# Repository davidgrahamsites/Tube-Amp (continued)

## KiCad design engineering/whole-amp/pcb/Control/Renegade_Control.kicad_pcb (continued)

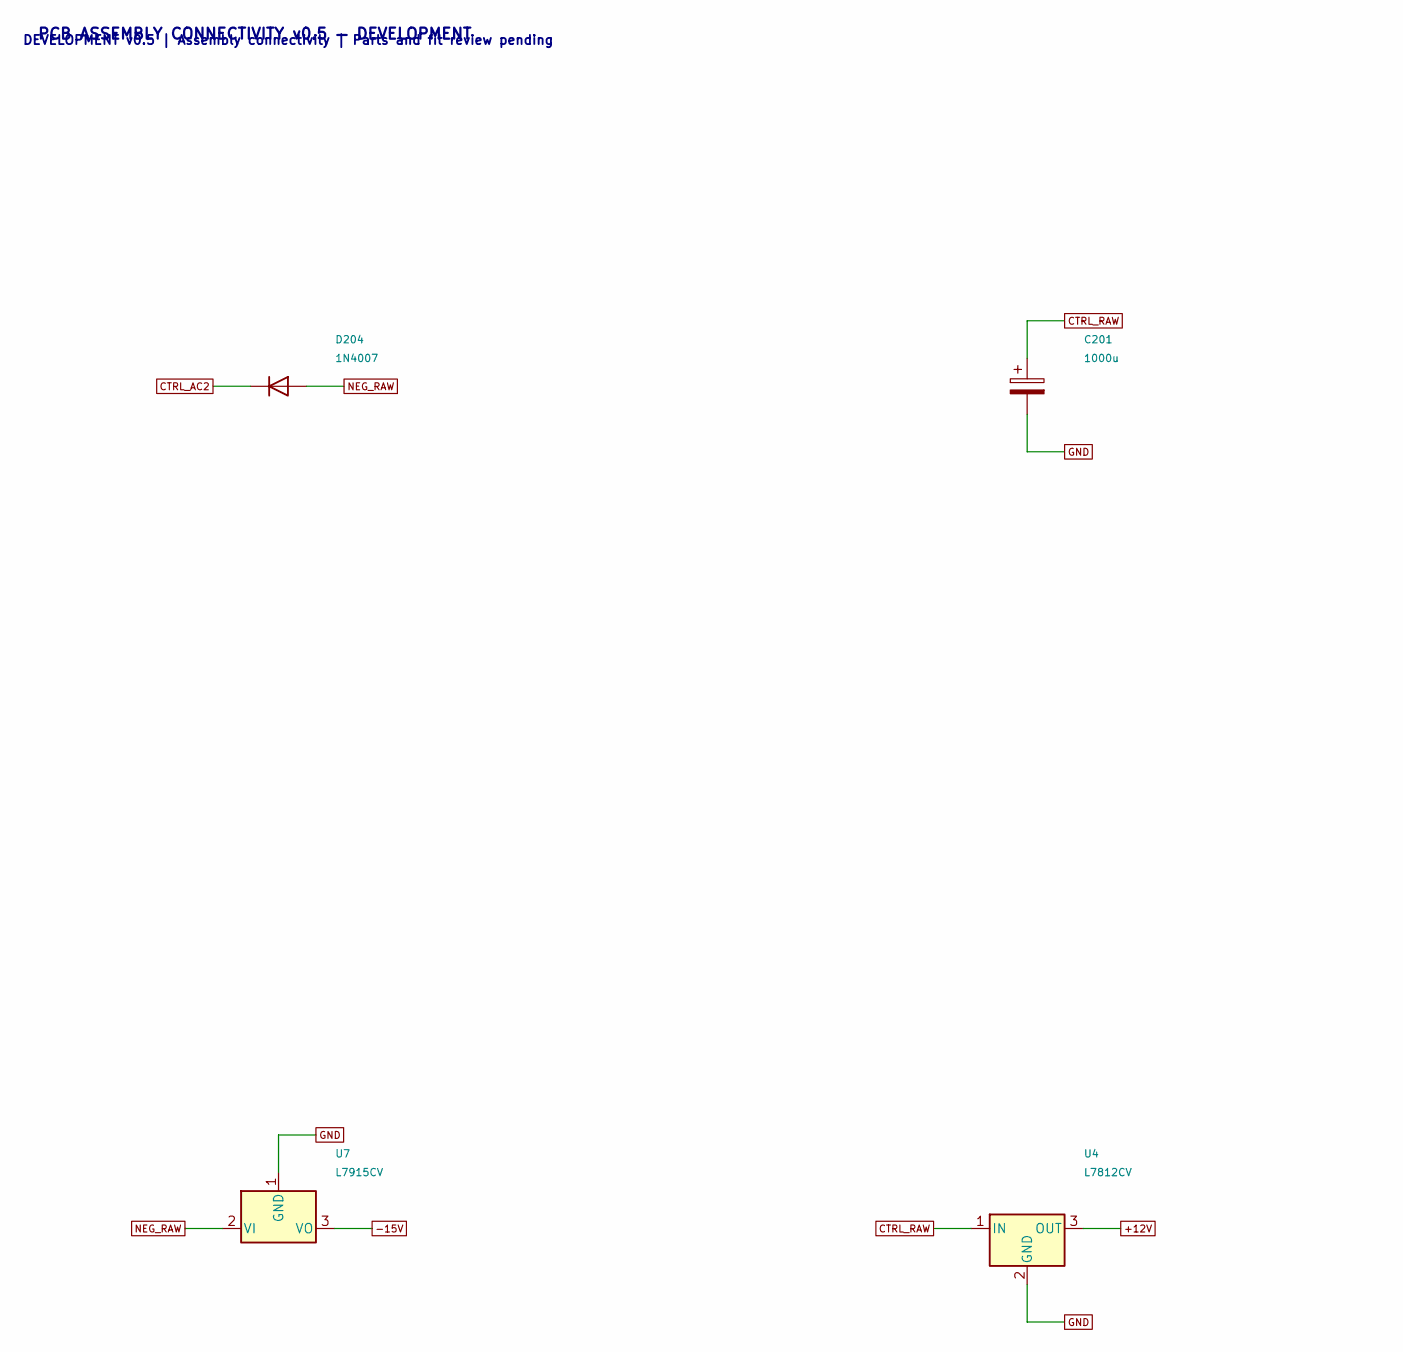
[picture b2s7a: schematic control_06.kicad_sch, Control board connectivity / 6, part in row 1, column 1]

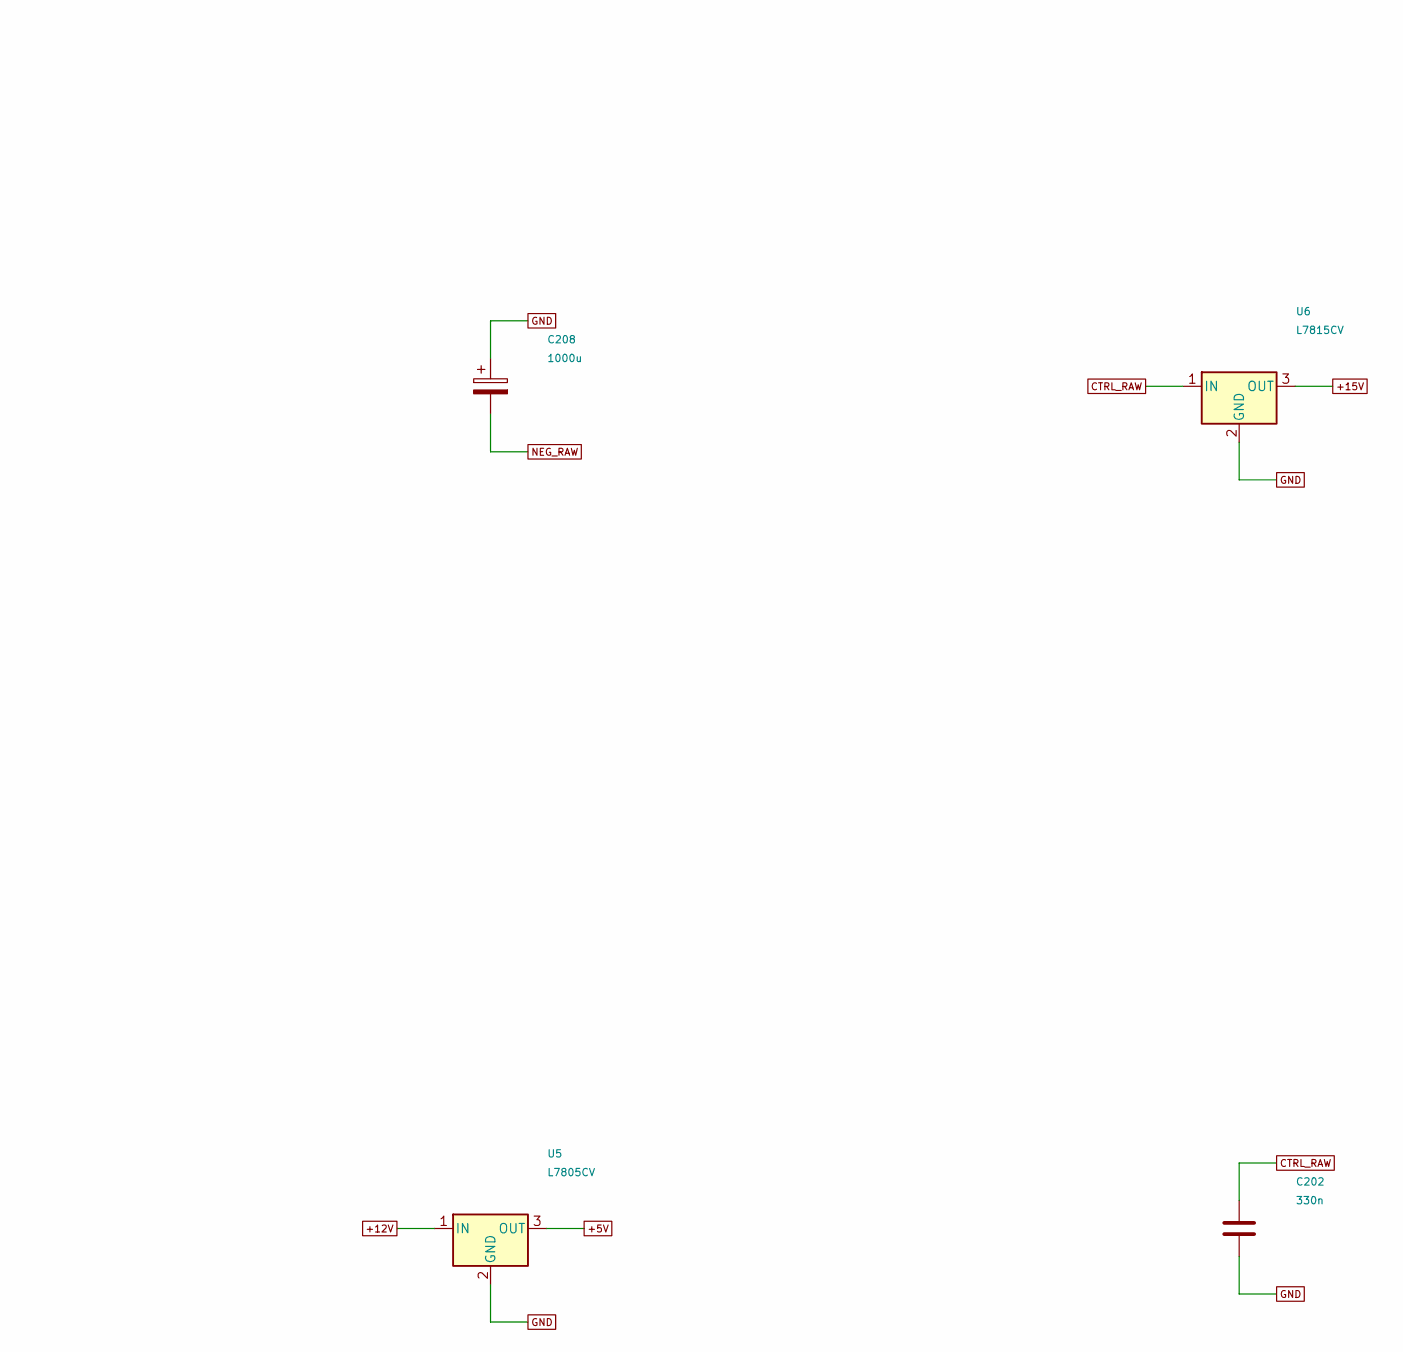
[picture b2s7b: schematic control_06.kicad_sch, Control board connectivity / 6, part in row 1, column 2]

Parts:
C201, C208: 1000u; CP_Radial_D16.0mm_P7.50mm; Rating 50V electrolytic, ripple rating required
C202: 330n; C_Rect_L7.2mm_W3.5mm_P5.00mm; Rating 63V film/C0G
D204: 1N4007; D_DO-41_SOD81_P10.16mm_Horizontal
U4: L7812CV; TO-220-3_Vertical; Rating TO220 heatsink; worst-case dissipation 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
U5: L7805CV; TO-220-3_Vertical
U6: L7815CV; TO-220-3_Vertical; Rating TO220 heatsink; ST datasheet
U7: L7915CV; TO-220-3_Vertical; Rating TO220 tab=negative input; isolated heat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

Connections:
+5V: U5.3 (OUT); also elsewhere on the board
+12V: U4.3 (OUT), U5.1 (IN); also elsewhere on the board
+15V: U6.3 (OUT); also elsewhere on the board
-15V: U7.3 (VO); also elsewhere on the board
CTRL_AC2: D204.1 (K); also elsewhere on the board
CTRL_RAW: C201.1, C202.1, U4.1 (IN), U6.1 (IN); also elsewhere on the board
GND: C201.2, C202.2, C208.1, U4.2 (GND), U5.2 (GND), U6.2 (GND), U7.1 (GND); also elsewhere on the board
NEG_RAW: C208.2, D204.2 (A), U7.2 (VI); also elsewhere on the board

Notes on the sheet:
PCB ASSEMBLY CONNECTIVITY v0.5 — DEVELOPMENT
DEVELOPMENT v0.5 | Assembly connectivity | Parts and fit review pending

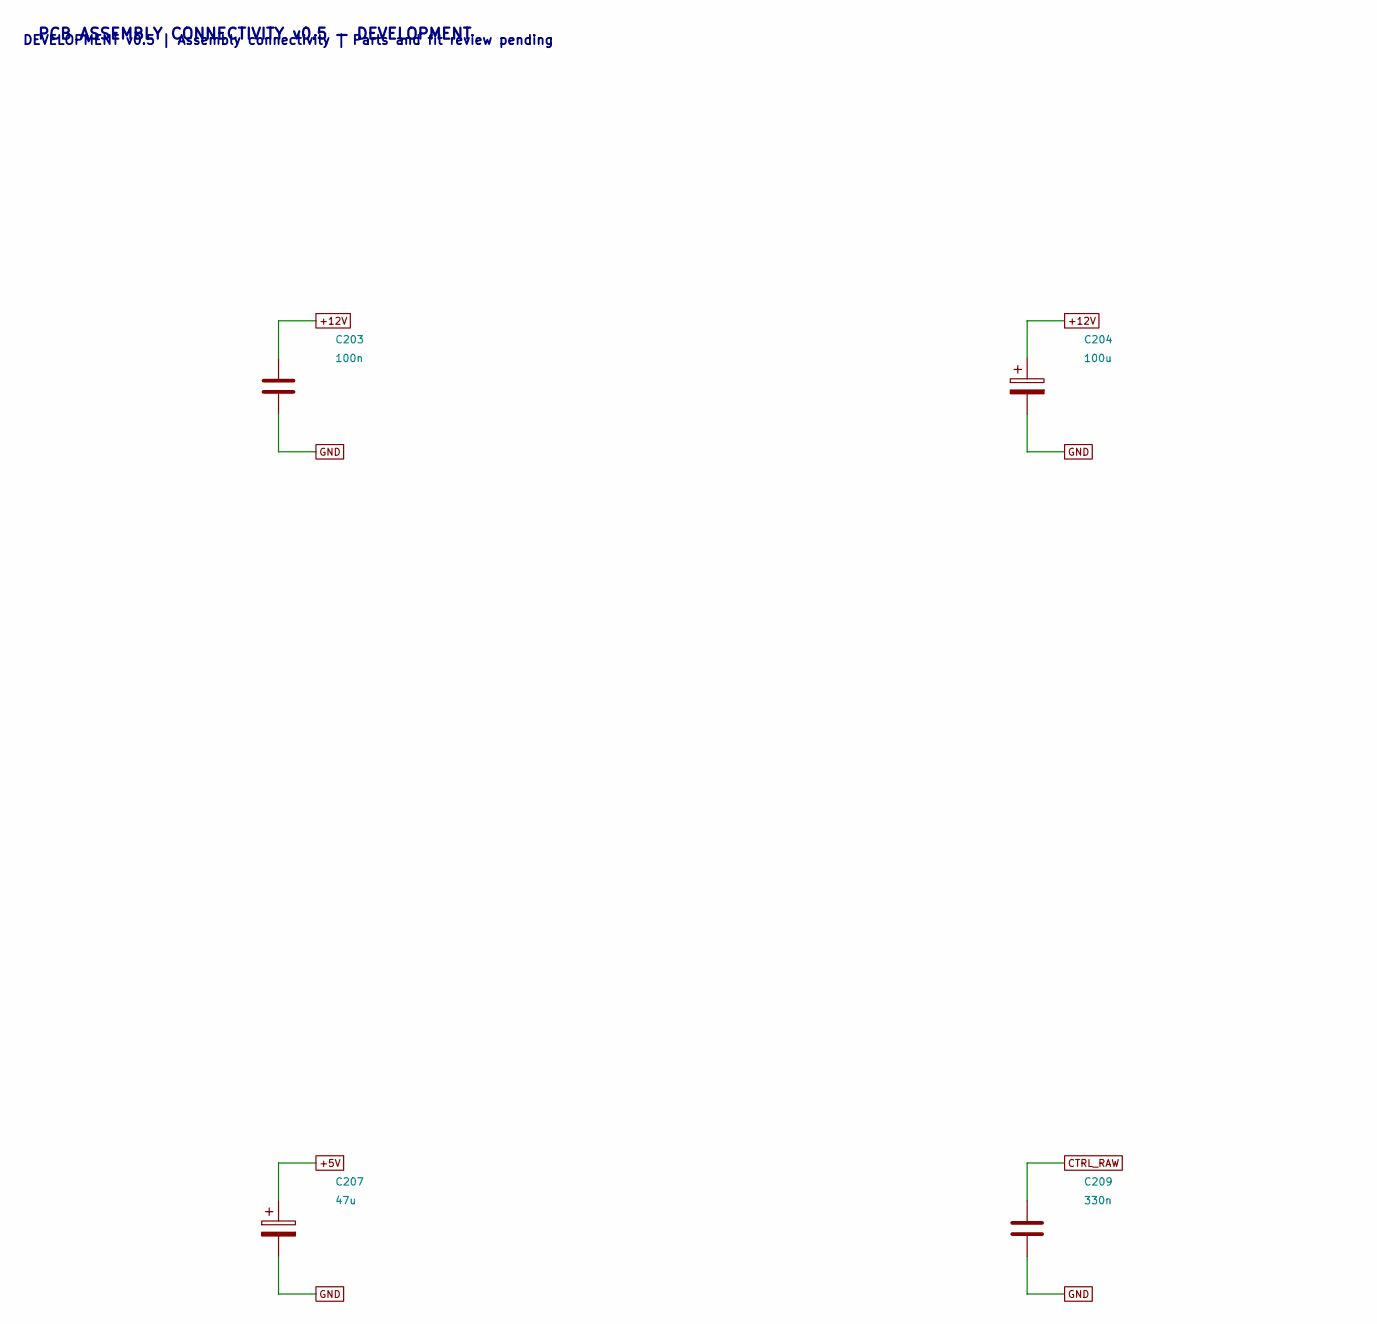
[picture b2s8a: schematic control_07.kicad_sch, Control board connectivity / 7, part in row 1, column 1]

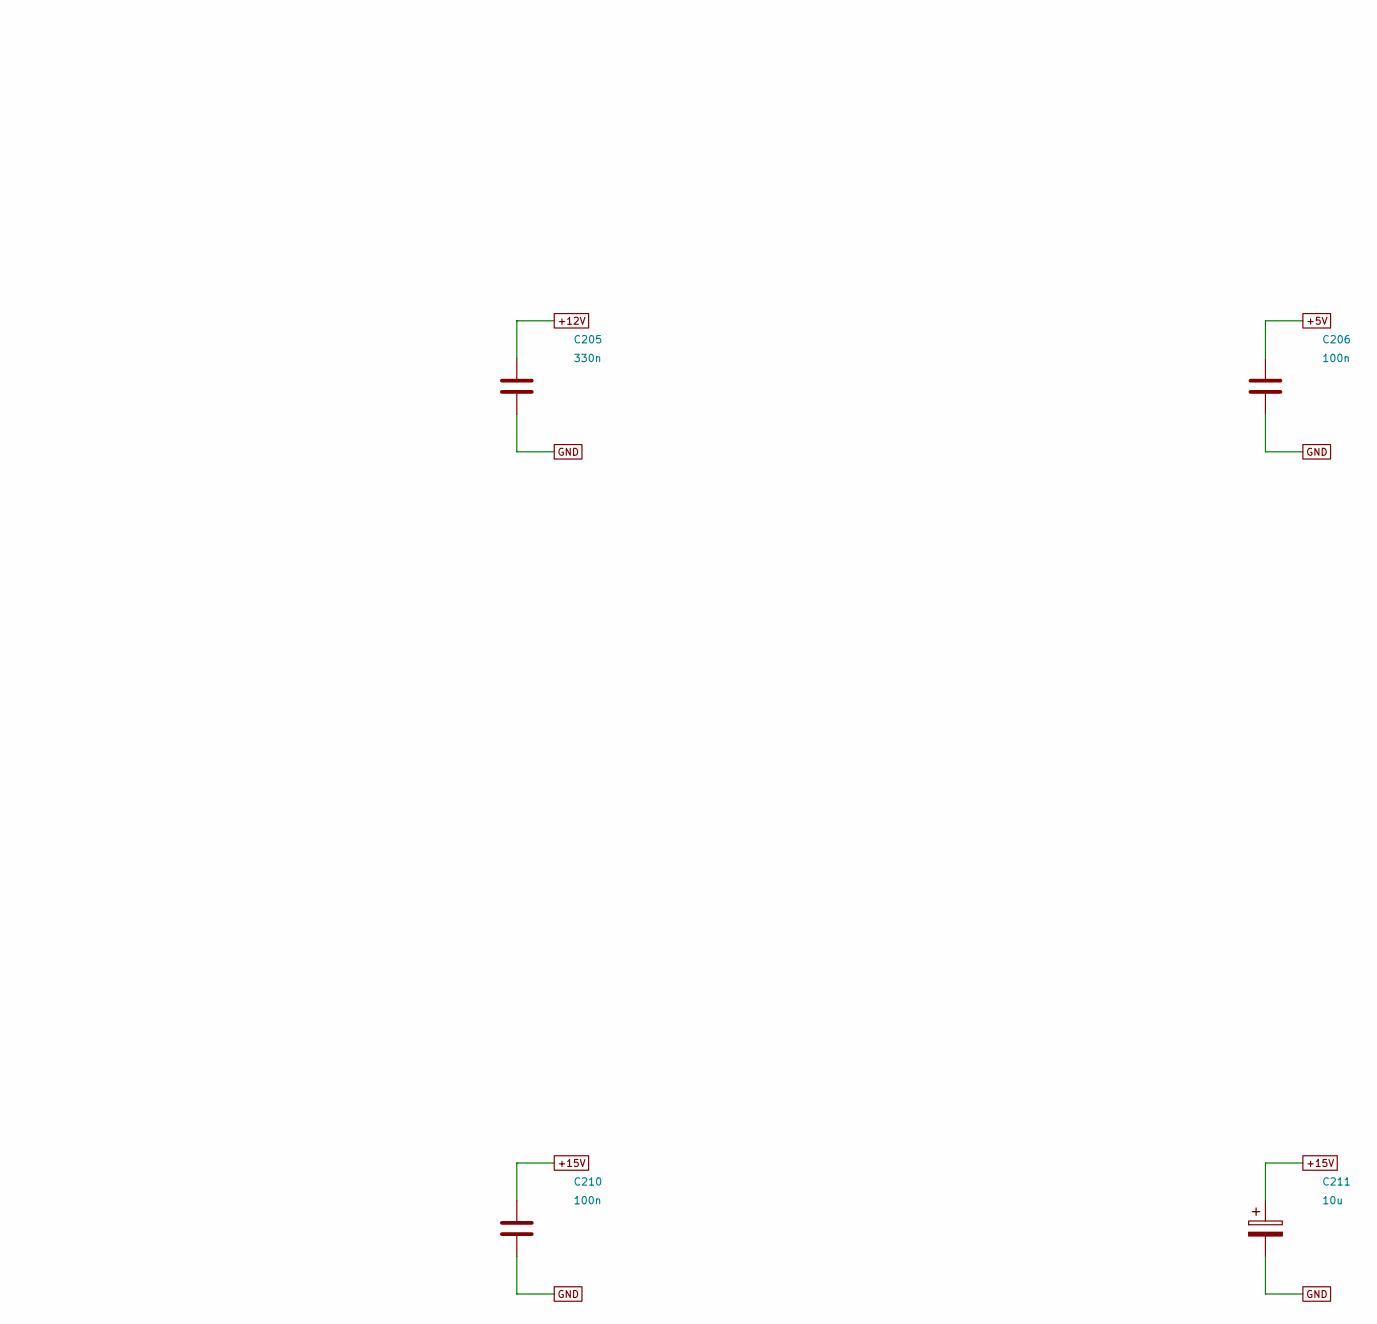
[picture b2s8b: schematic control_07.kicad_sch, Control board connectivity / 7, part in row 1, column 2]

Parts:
C203, C206, C210: 100n; C_Rect_L7.2mm_W3.5mm_P5.00mm; Rating 63V film/C0G
C204: 100u; CP_Radial_D8.0mm_P3.50mm; Rating 50V electrolytic
C205, C209: 330n; C_Rect_L7.2mm_W3.5mm_P5.00mm; Rating 63V film/C0G
C207: 47u; CP_Radial_D8.0mm_P3.50mm; Rating 50V electrolytic
C211: 10u; CP_Radial_D8.0mm_P3.50mm; Rating 50V electrolytic

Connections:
+5V: C206.1, C207.1; also elsewhere on the board
+12V: C203.1, C204.1, C205.1; also elsewhere on the board
+15V: C210.1, C211.1; also elsewhere on the board
CTRL_RAW: C209.1; also elsewhere on the board
GND: C203.2, C204.2, C205.2, C206.2, C207.2, C209.2, C210.2, C211.2; also elsewhere on the board

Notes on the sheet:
PCB ASSEMBLY CONNECTIVITY v0.5 — DEVELOPMENT
DEVELOPMENT v0.5 | Assembly connectivity | Parts and fit review pending

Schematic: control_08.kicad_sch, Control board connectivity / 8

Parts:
C212: 2.2u; CP_Radial_D8.0mm_P3.50mm; Rating 50V electrolytic
C213: 100n; C_Rect_L7.2mm_W3.5mm_P5.00mm; Rating 63V film/C0G
C214: 10u; CP_Radial_D8.0mm_P3.50mm; Rating 50V electrolytic
D205, D206, D207, D208: 1N4007; D_DO-41_SOD81_P10.16mm_Horizontal
JC001: +12V; WirePad_1.3mm; Rating Soldered and strain-relieved wire, volt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

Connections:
+5V: D206.2 (A); also elsewhere on the board
+12V: D205.2 (A), D206.1 (K), JC001.1; also elsewhere on the board
+15V: D207.2 (A); also elsewhere on the board
-15V: C213.2, C214.2, D208.1 (K); also elsewhere on the board
CTRL_RAW: D205.1 (K), D207.1 (K); also elsewhere on the board
GND: C212.1, C213.1, C214.1; also elsewhere on the board
NEG_RAW: C212.2, D208.2 (A); also elsewhere on the board

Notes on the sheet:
PCB ASSEMBLY CONNECTIVITY v0.5 — DEVELOPMENT
DEVELOPMENT v0.5 | Assembly connectivity | Parts and fit review pending

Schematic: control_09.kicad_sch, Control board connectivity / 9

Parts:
JC002: +15V; WirePad_1.3mm; Rating Soldered and strain-relieved wire, volt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
JC003: -15V; WirePad_1.3mm; Rating Soldered and strain-relieved wire, volt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
JC004: BTN_CH; WirePad_1.3mm; Rating Soldered and strain-relieved wire, volt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
JC005: BTN_REV; WirePad_1.3mm; Rating Soldered and strain-relieved wire, volt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
JC006: COIL_CH; WirePad_1.3mm; Rating Soldered and strain-relieved wire, volt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
JC007: COIL_REV; WirePad_1.3mm; Rating Soldered and strain-relieved wire, volt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
JC008: CTRL_AC1; WirePad_1.3mm; Rating Soldered and strain-relieved wire, volt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
JC009: CTRL_AC2; WirePad_1.3mm; Rating Soldered and strain-relieved wire, volt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

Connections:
+15V: JC002.1; also elsewhere on the board
-15V: JC003.1; also elsewhere on the board
BTN_CH: JC004.1; also elsewhere on the board
BTN_REV: JC005.1; also elsewhere on the board
COIL_CH: JC006.1; also elsewhere on the board
COIL_REV: JC007.1; also elsewhere on the board
CTRL_AC1: JC008.1; also elsewhere on the board
CTRL_AC2: JC009.1; also elsewhere on the board

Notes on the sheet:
PCB ASSEMBLY CONNECTIVITY v0.5 — DEVELOPMENT
DEVELOPMENT v0.5 | Assembly connectivity | Parts and fit review pending

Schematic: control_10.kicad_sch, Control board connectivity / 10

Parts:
H1, H2, H3, H4: MountingHole_3.2mm_M3
JC010: GND; WirePad_1.3mm; Rating Soldered and strain-relieved wire, volt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
JC011: MR_N; WirePad_1.3mm; Rating Soldered and strain-relieved wire, volt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
JC012: PEDAL_CH; WirePad_1.3mm; Rating Soldered and strain-relieved wire, volt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
JC013: PEDAL_REV; WirePad_1.3mm; Rating Soldered and strain-relieved wire, volt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

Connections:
GND: JC010.1; also elsewhere on the board
MR_N: JC011.1; also elsewhere on the board
PEDAL_CH: JC012.1; also elsewhere on the board
PEDAL_REV: JC013.1; also elsewhere on the board

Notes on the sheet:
PCB ASSEMBLY CONNECTIVITY v0.5 — DEVELOPMENT
DEVELOPMENT v0.5 | Assembly connectivity | Parts and fit review pending

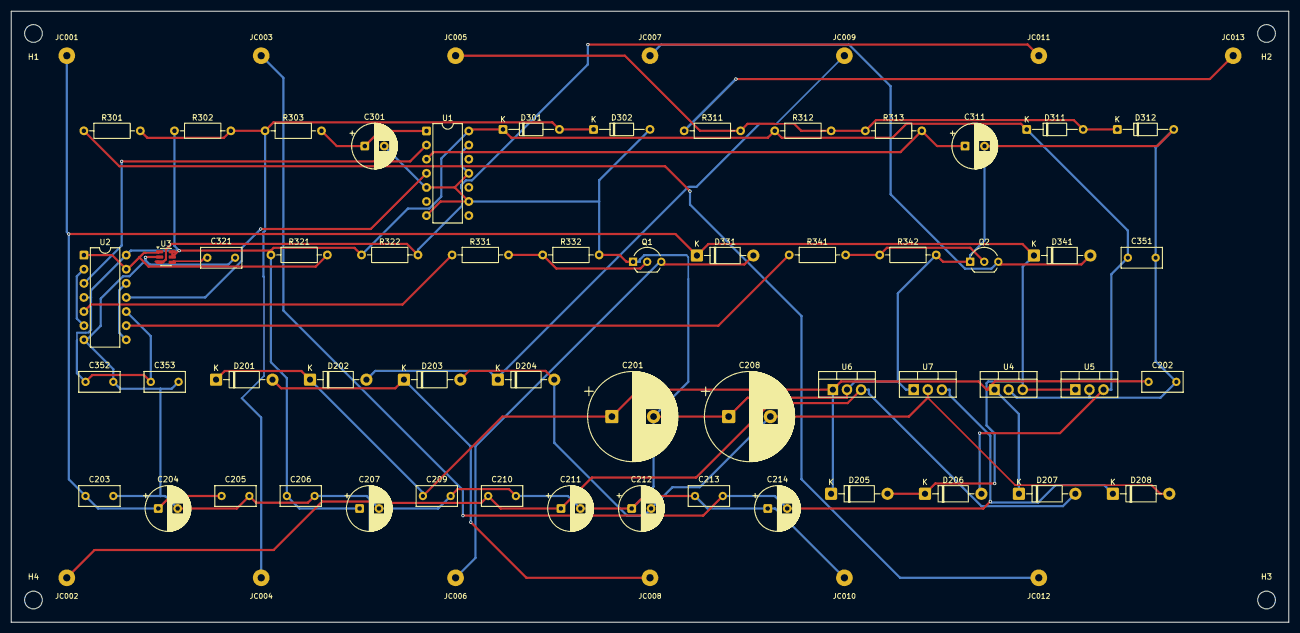
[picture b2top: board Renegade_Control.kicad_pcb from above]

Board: 2 copper layers, 230.0 x 110.0 mm, 72 parts (0 on the bottom side), 28 nets.

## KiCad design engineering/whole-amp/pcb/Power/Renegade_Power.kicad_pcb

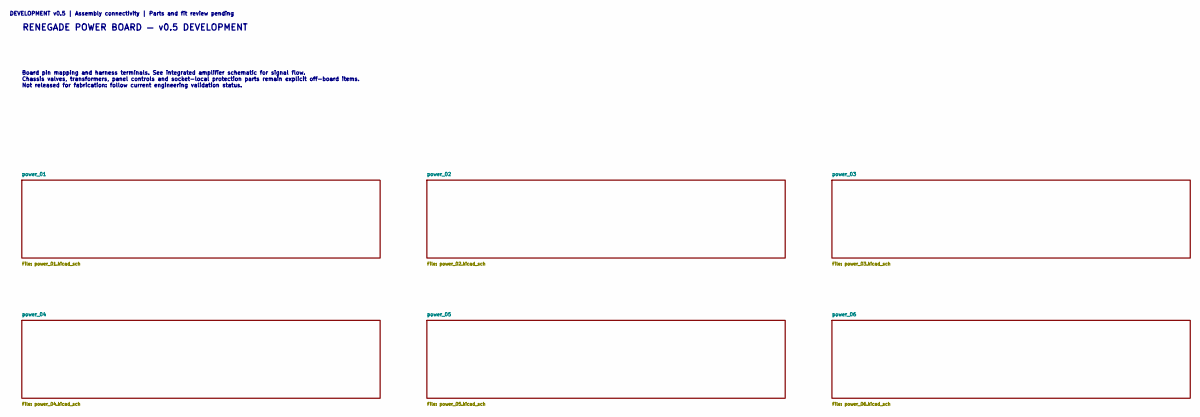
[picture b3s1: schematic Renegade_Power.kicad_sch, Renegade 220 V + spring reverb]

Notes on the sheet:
RENEGADE POWER BOARD — v0.5 DEVELOPMENT
Board pin mapping and harness terminals. See integrated amplifier schematic for signal flow. Chassis valves, transformers, panel controls and socket-local protection parts remain explicit off-board items. Not released for fabrication: follow current engineering validation status.
DEVELOPMENT v0.5 | Assembly connectivity | Parts and fit review pending

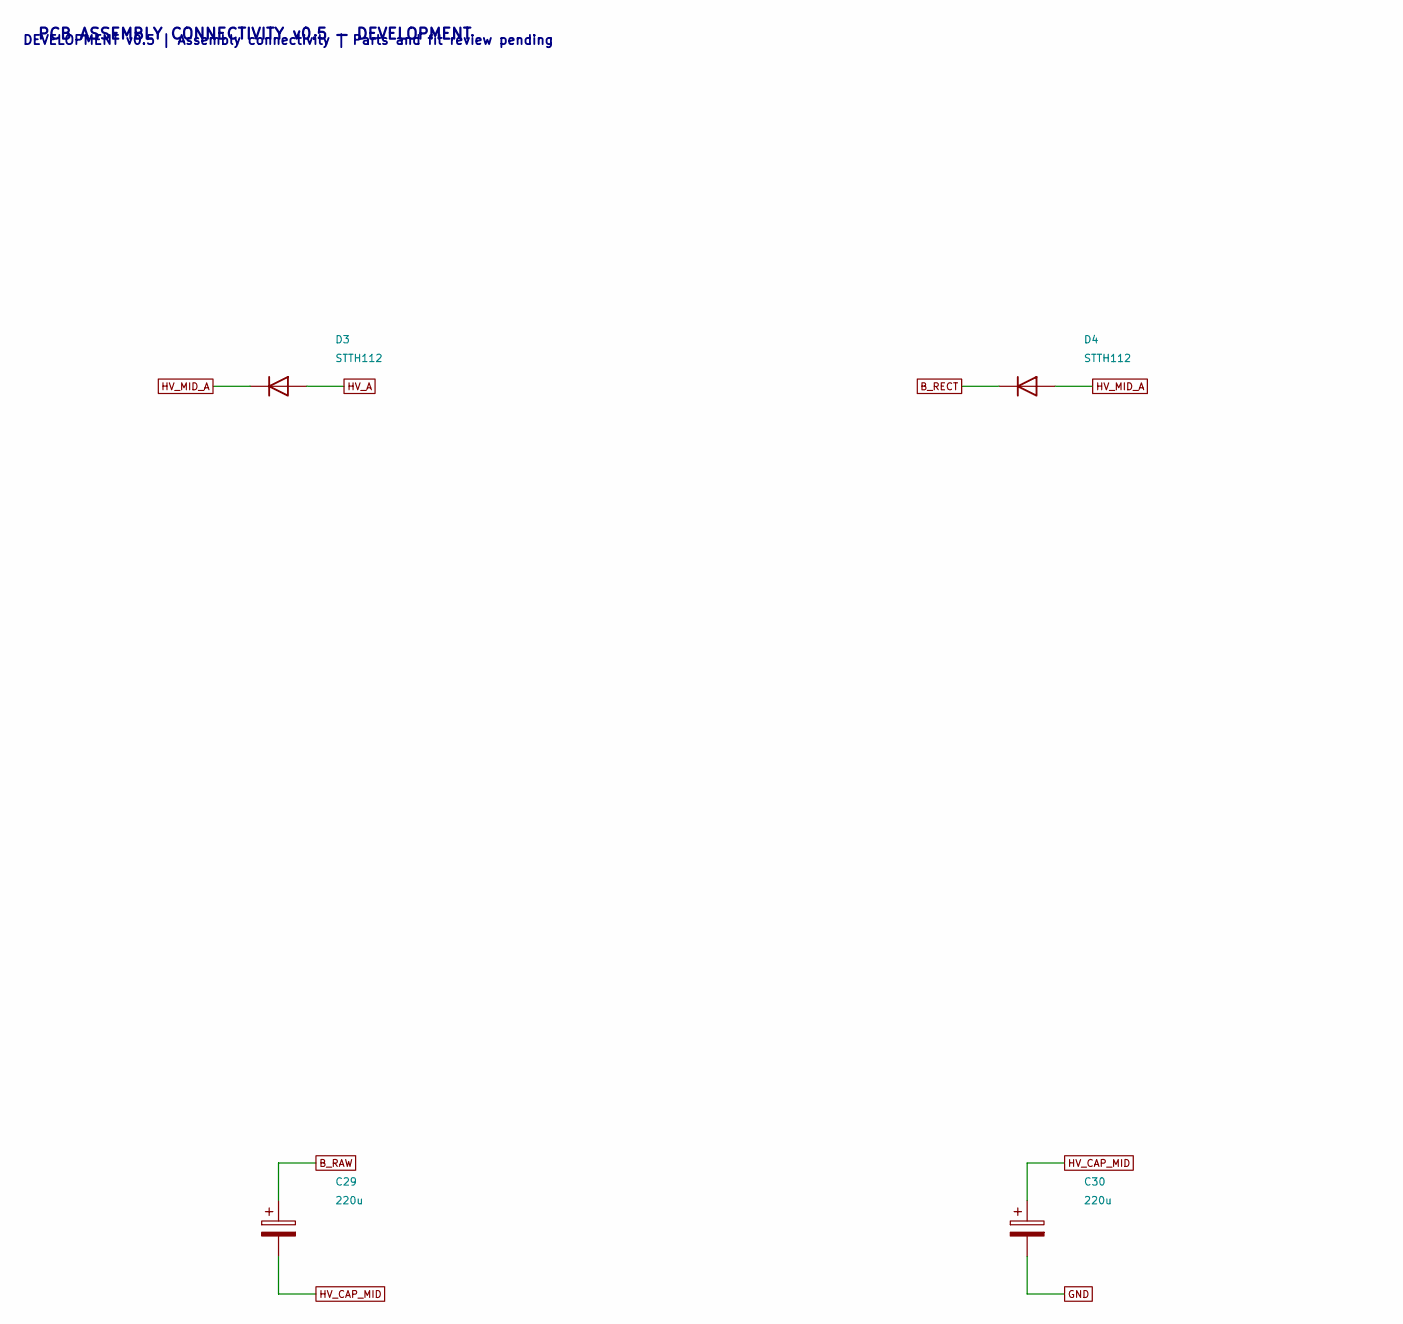
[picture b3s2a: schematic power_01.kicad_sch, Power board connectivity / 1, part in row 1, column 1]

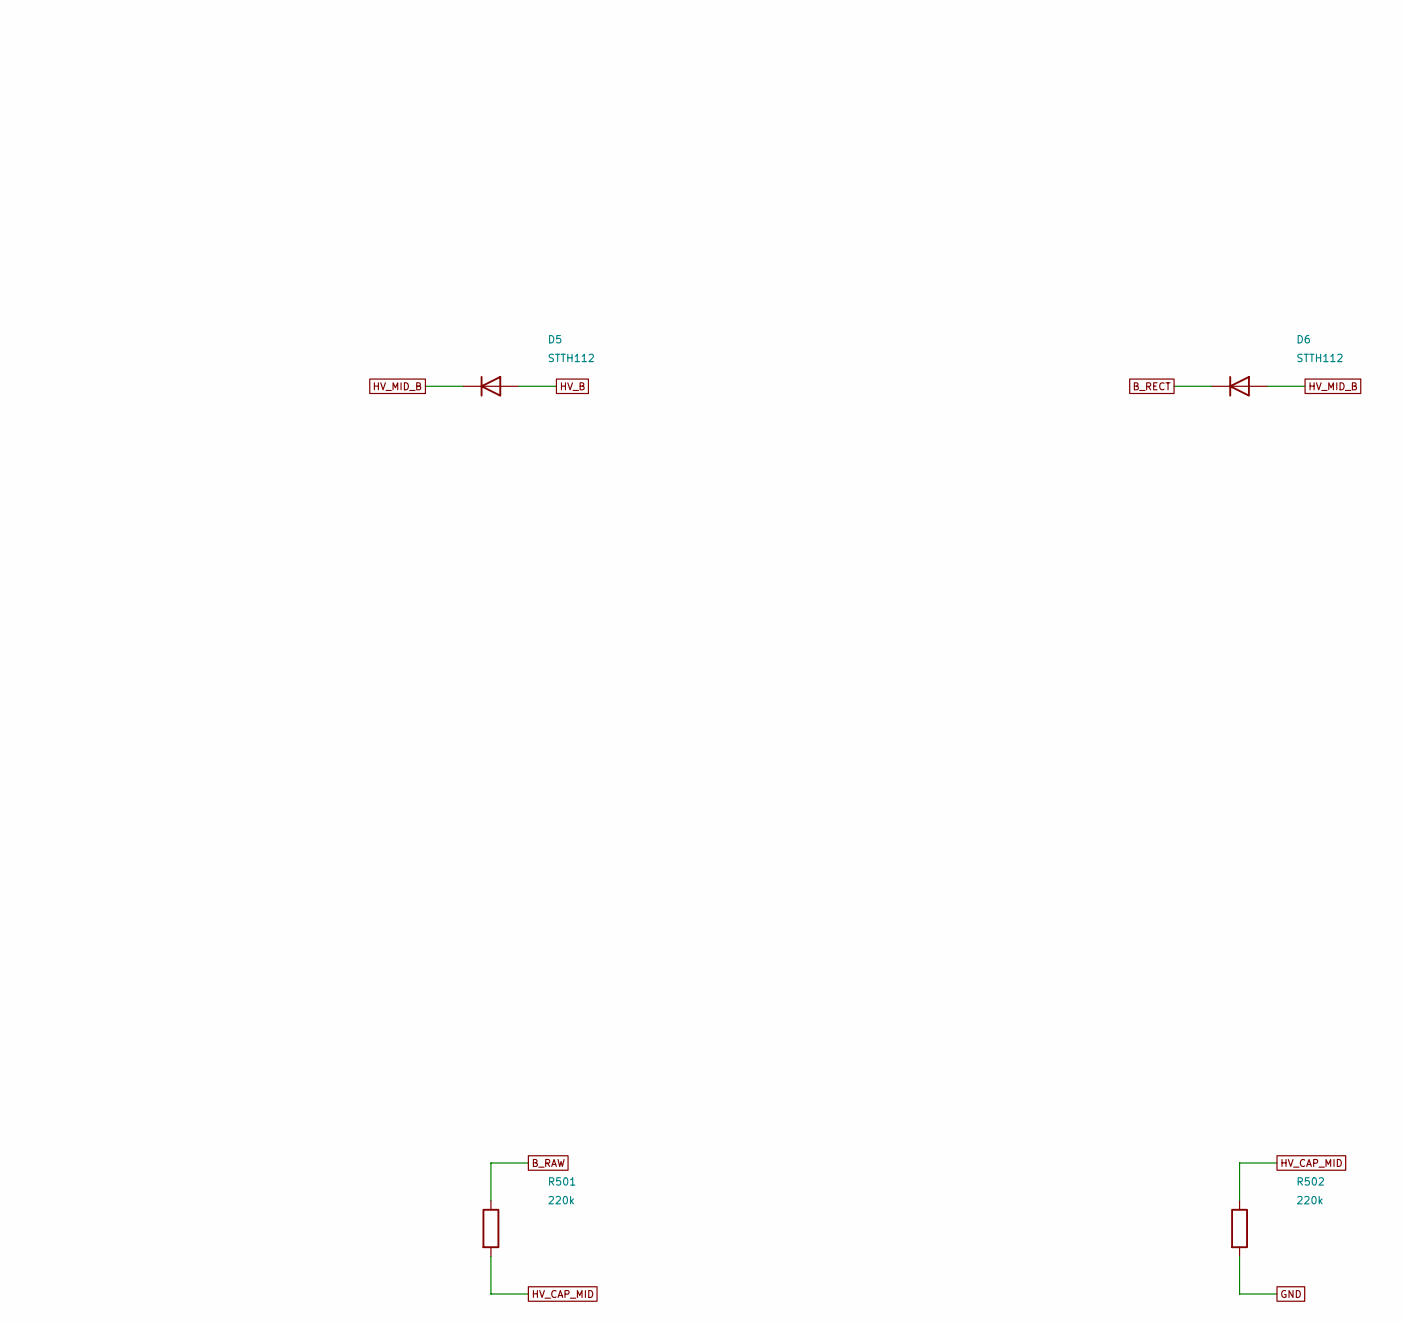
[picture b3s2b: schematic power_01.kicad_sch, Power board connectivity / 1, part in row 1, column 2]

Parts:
C29, C30: 220u; CP_Radial_D22.0mm_P10.00mm_SnapIn; Rating 220uF 400V; 22x30mm nominal, max23.5x32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
D3, D4, D5, D6: STTH112; D_DO-41_SOD81_P12.70mm_Horizontal; Rating 1200V 1A DO41; axial part, not STTH112A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
R501, R502: 220k; R_Axial_DIN0414_L11.9mm_D4.5mm_P15.24mm_Horizontal; Rating 2 W; 350 V working minimum

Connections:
B_RAW: C29.1, R501.1; also elsewhere on the board
B_RECT: D4.1 (K), D6.1 (K); also elsewhere on the board
GND: C30.2, R502.2; also elsewhere on the board
HV_A: D3.2 (A); also elsewhere on the board
HV_B: D5.2 (A); also elsewhere on the board
HV_CAP_MID: C29.2, C30.1, R501.2, R502.1
HV_MID_A: D3.1 (K), D4.2 (A)
HV_MID_B: D5.1 (K), D6.2 (A)

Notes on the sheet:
PCB ASSEMBLY CONNECTIVITY v0.5 — DEVELOPMENT
DEVELOPMENT v0.5 | Assembly connectivity | Parts and fit review pending

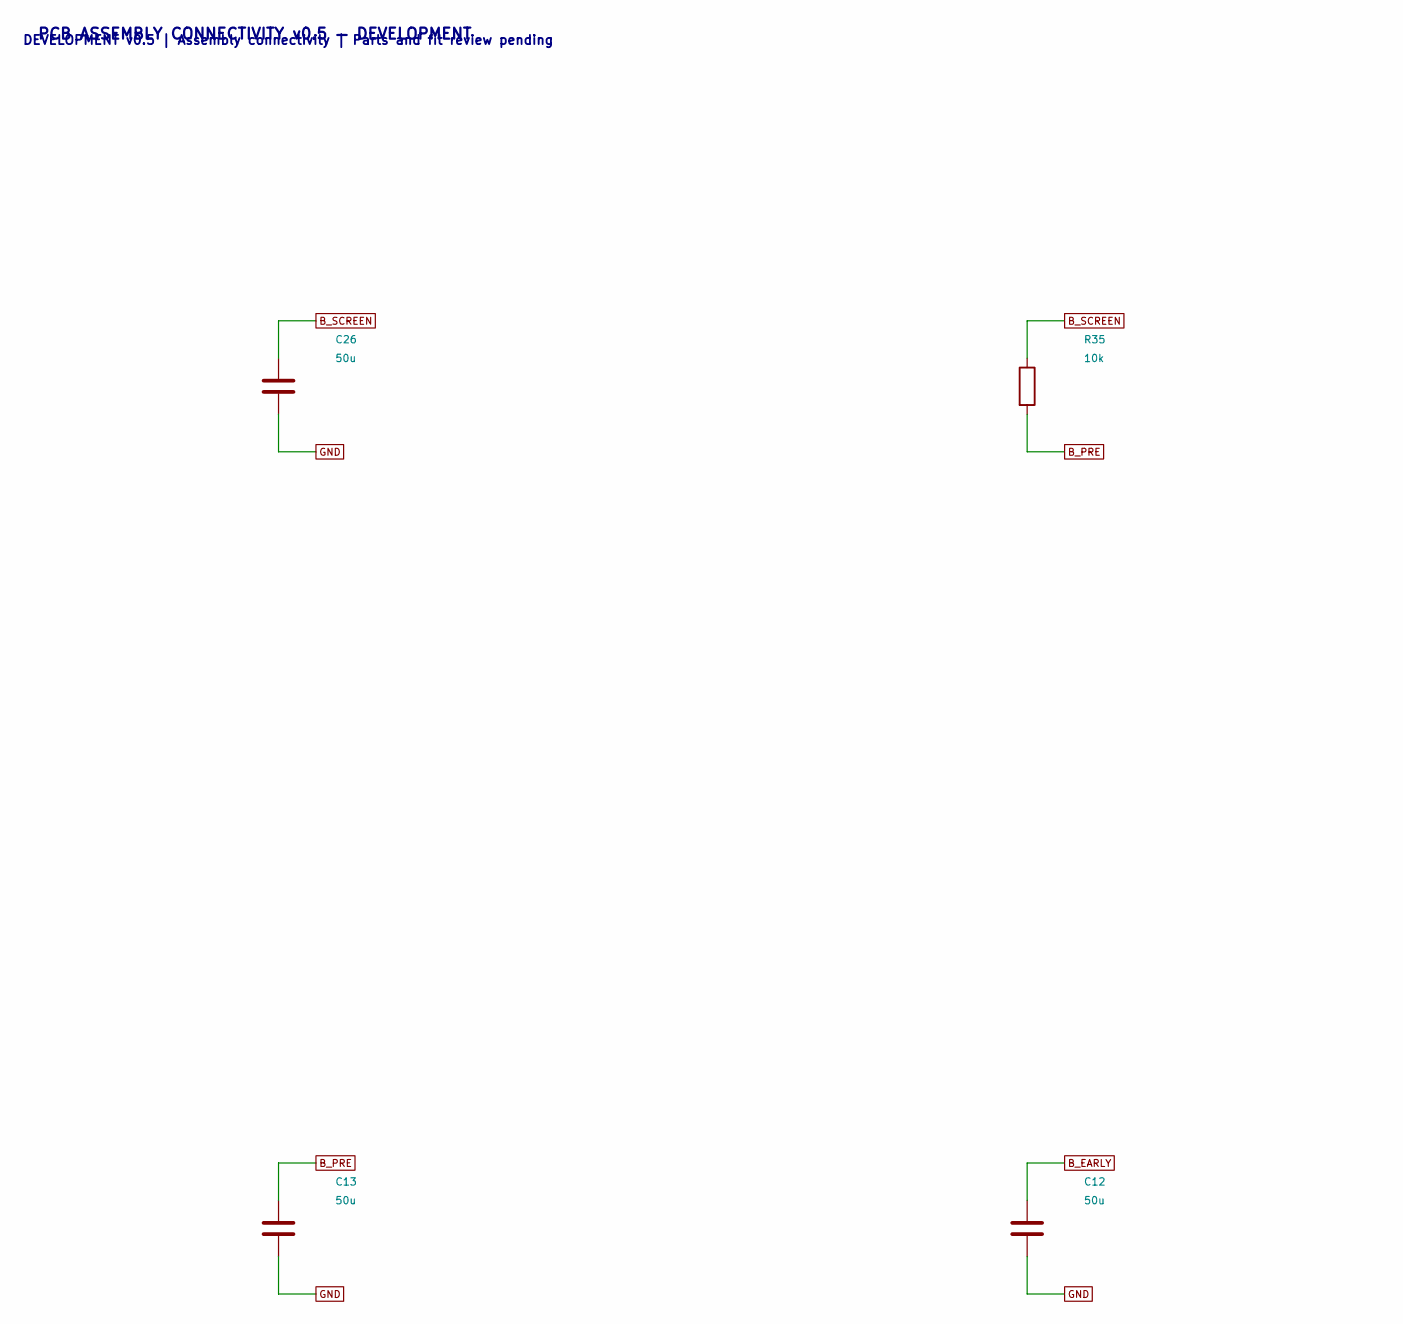
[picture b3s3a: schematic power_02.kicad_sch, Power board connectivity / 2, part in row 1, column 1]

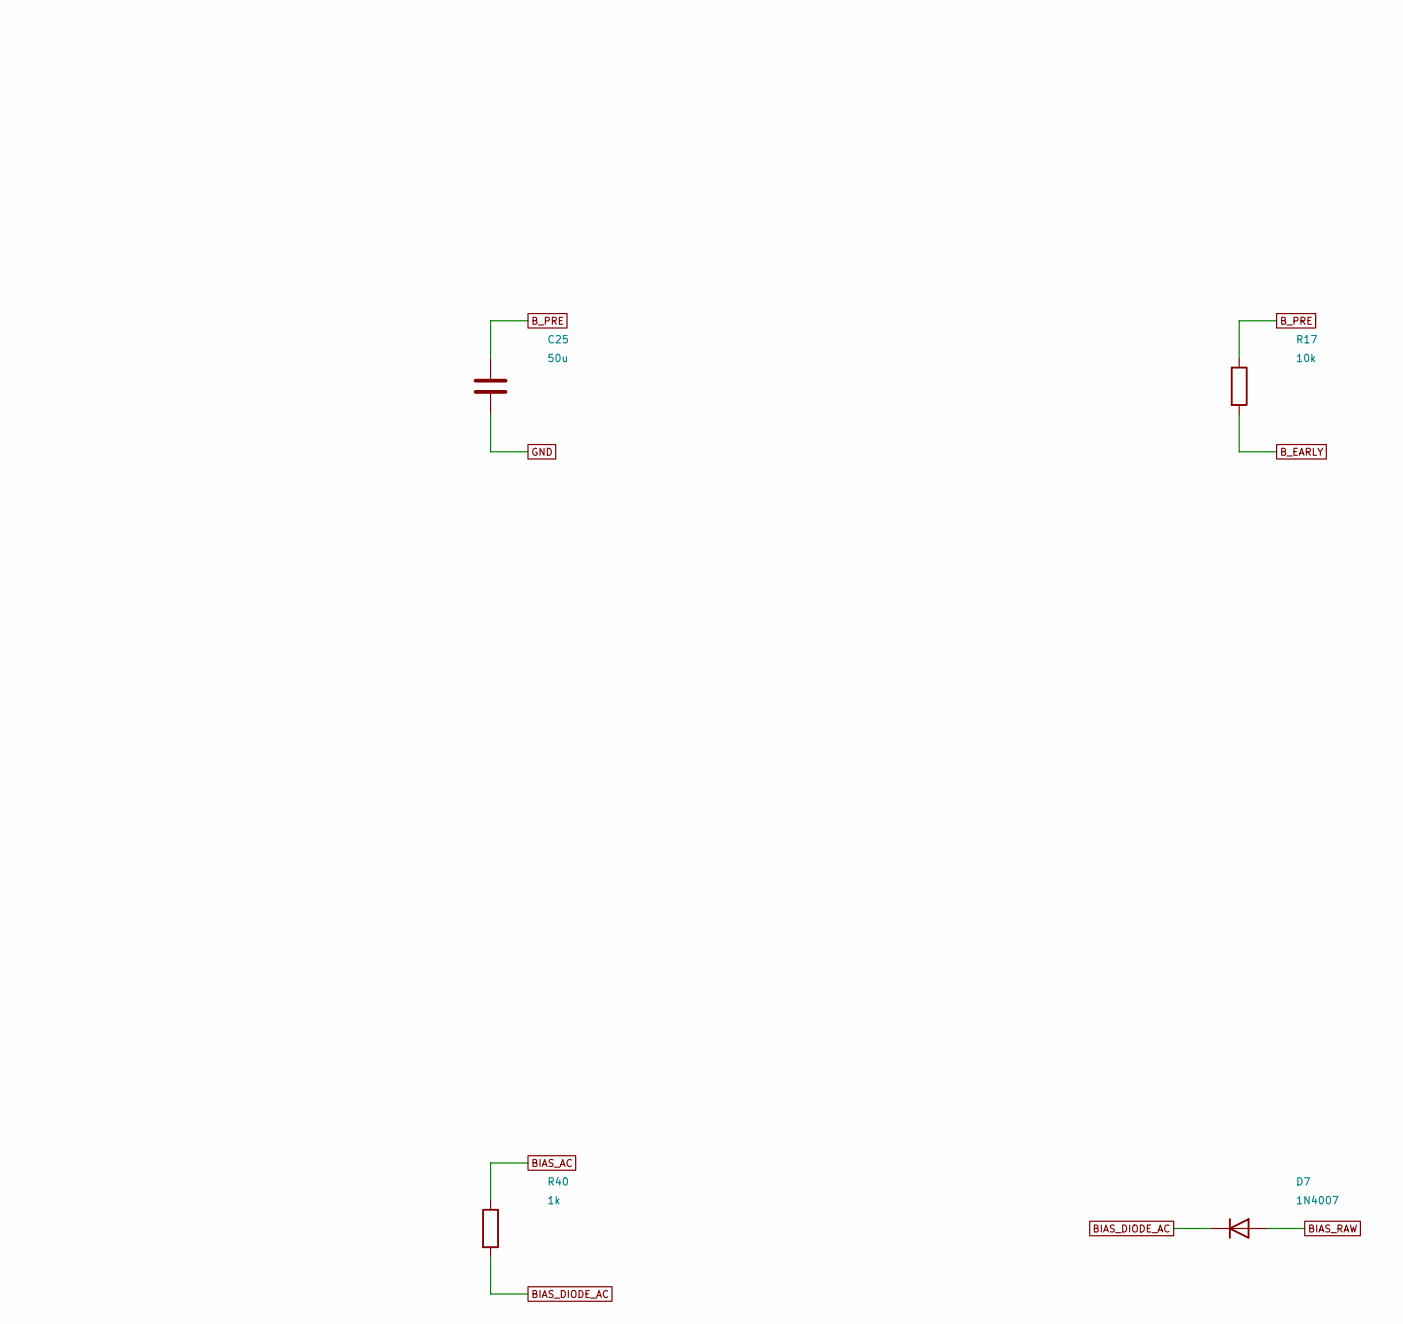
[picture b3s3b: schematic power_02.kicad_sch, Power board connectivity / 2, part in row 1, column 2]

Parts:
C12, C13, C25, C26: 50u; Panasonic_EZPV60506MTC; Rating 50uF 600VDC film; official RDL0000C251 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
D7: 1N4007; D_DO-41_SOD81_P10.16mm_Horizontal
R17, R35: 10k; R_Axial_DIN0414_L11.9mm_D4.5mm_P15.24mm_Horizontal; Rating 5 W
R40: 1k; R_Axial_DIN0207_L6.3mm_D2.5mm_P15.24mm_Horizontal; Rating 1 W

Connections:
BIAS_AC: R40.1; also elsewhere on the board
BIAS_DIODE_AC: D7.1 (K), R40.2
BIAS_RAW: D7.2 (A); also elsewhere on the board
B_EARLY: C12.1, R17.2; also elsewhere on the board
B_PRE: C13.1, C25.1, R17.1, R35.2; also elsewhere on the board
B_SCREEN: C26.1, R35.1; also elsewhere on the board
GND: C12.2, C13.2, C25.2, C26.2; also elsewhere on the board

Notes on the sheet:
PCB ASSEMBLY CONNECTIVITY v0.5 — DEVELOPMENT
DEVELOPMENT v0.5 | Assembly connectivity | Parts and fit review pending

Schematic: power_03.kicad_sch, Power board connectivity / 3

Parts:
C27, C28: 10u; CP_Radial_D10.0mm_P5.00mm; Rating 100 V
R38: 22k; R_Axial_DIN0207_L6.3mm_D2.5mm_P15.24mm_Horizontal; Rating 1 W
R39: 4.7k; R_Axial_DIN0207_L6.3mm_D2.5mm_P15.24mm_Horizontal; Rating 1 W
R503: 33k; R_Axial_DIN0207_L6.3mm_D2.5mm_P15.24mm_Horizontal; Rating 1 W; minimum negative-bias stop
R506: 220k; R_Axial_DIN0414_L11.9mm_D4.5mm_P15.24mm_Horizontal; Rating 2 W; voltage rating pending
R507: 39k; R_Axial_DIN0207_L6.3mm_D2.5mm_P15.24mm_Horizontal; Rating 1 W
RV10: 50k LIN BIAS; Potentiometer_Bourns_3296W_Vertical; Rating Off-board; voltage, taper and drawing r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

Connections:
BIAS_FILTER: C27.2, R38.1, R39.2
BIAS_MIN: R503.1, RV10.2, RV10.3
BIAS_OUT: R38.2, RV10.1; also elsewhere on the board
BIAS_RAW: C28.2, R39.1; also elsewhere on the board
B_SCREEN: R506.1; also elsewhere on the board
GND: C27.1, C28.1, R503.2, R507.2; also elsewhere on the board
HREF: R506.2, R507.1; also elsewhere on the board

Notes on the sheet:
PCB ASSEMBLY CONNECTIVITY v0.5 — DEVELOPMENT
DEVELOPMENT v0.5 | Assembly connectivity | Parts and fit review pending

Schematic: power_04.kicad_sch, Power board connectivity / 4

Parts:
C505: 47u; CP_Radial_D10.0mm_P5.00mm; Rating 160 V
JP001: BIAS_AC; WirePad_1.3mm; Rating Soldered and strain-relieved wire, volt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
JP002: BIAS_OUT; WirePad_1.3mm; Rating Soldered and strain-relieved wire, volt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
JP003: B_EARLY; WirePad_1.3mm; Rating Soldered and strain-relieved wire, volt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
JP004: B_PRE; WirePad_1.3mm; Rating Soldered and strain-relieved wire, volt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
JP005: B_RAW; WirePad_1.3mm; Rating Soldered and strain-relieved wire, volt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
R508, R509: 100; R_Axial_DIN0207_L6.3mm_D2.5mm_P15.24mm_Horizontal; Rating 0.5 W

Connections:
BIAS_AC: JP001.1; also elsewhere on the board
BIAS_OUT: JP002.1; also elsewhere on the board
B_EARLY: JP003.1; also elsewhere on the board
B_PRE: JP004.1; also elsewhere on the board
B_RAW: JP005.1; also elsewhere on the board
GND: C505.2; also elsewhere on the board
HEAT_A: R508.1; also elsewhere on the board
HEAT_B: R509.1; also elsewhere on the board
HREF: C505.1, R508.2, R509.2; also elsewhere on the board

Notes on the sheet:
PCB ASSEMBLY CONNECTIVITY v0.5 — DEVELOPMENT
DEVELOPMENT v0.5 | Assembly connectivity | Parts and fit review pending

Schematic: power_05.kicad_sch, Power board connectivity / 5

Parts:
H1: MountingHole_3.2mm_M3
JP006: B_RECT; WirePad_1.3mm; Rating Soldered and strain-relieved wire, volt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
JP007: B_SCREEN; WirePad_1.3mm; Rating Soldered and strain-relieved wire, volt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
JP008: GND; WirePad_1.3mm; Rating Soldered and strain-relieved wire, volt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
JP009: HEAT_A; WirePad_1.3mm; Rating Soldered and strain-relieved wire, volt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
JP010: HEAT_B; WirePad_1.3mm; Rating Soldered and strain-relieved wire, volt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
JP011: HV_A; WirePad_1.3mm; Rating Soldered and strain-relieved wire, volt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
JP012: HV_B; WirePad_1.3mm; Rating Soldered and strain-relieved wire, volt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

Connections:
B_RECT: JP006.1; also elsewhere on the board
B_SCREEN: JP007.1; also elsewhere on the board
GND: JP008.1; also elsewhere on the board
HEAT_A: JP009.1; also elsewhere on the board
HEAT_B: JP010.1; also elsewhere on the board
HV_A: JP011.1; also elsewhere on the board
HV_B: JP012.1; also elsewhere on the board

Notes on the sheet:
PCB ASSEMBLY CONNECTIVITY v0.5 — DEVELOPMENT
DEVELOPMENT v0.5 | Assembly connectivity | Parts and fit review pending

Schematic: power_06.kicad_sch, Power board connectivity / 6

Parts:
H2, H3, H4: MountingHole_3.2mm_M3

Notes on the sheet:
PCB ASSEMBLY CONNECTIVITY v0.5 — DEVELOPMENT
DEVELOPMENT v0.5 | Assembly connectivity | Parts and fit review pending
